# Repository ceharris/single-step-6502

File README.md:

single-step-6502
================

This repository contains KiCad sources for a simple single-step controller
module for the 6502 microprocessor. It's designed to be connected to the
system under test using jumpers. It has a pin header that provides +5 VDC,
ground, and the 6502's SYNC and RDY signal paths.

The controller has two push buttons.

1. **Run/Stop** -- is used to toggle between the free running and 
   single-step modes. In the free running mode, the green status LED is 
   illuminated.
2. **Step** -- is used to advance the processor by a single instruction when
   the CPU is stopped. While the CPU is stopped, the red status LED is 
   illuminated.

The buttons are debounced via the 555 and 74123 ICs to avoid triggering
multiple step pulses.

The circuit is designed with a diode such that it can be connected to the 
6502's RDY input without disrupting other uses of the signal.

See [single-step-6502.pdf](single-step-6502.pdf) for a full description
of the circuit design.

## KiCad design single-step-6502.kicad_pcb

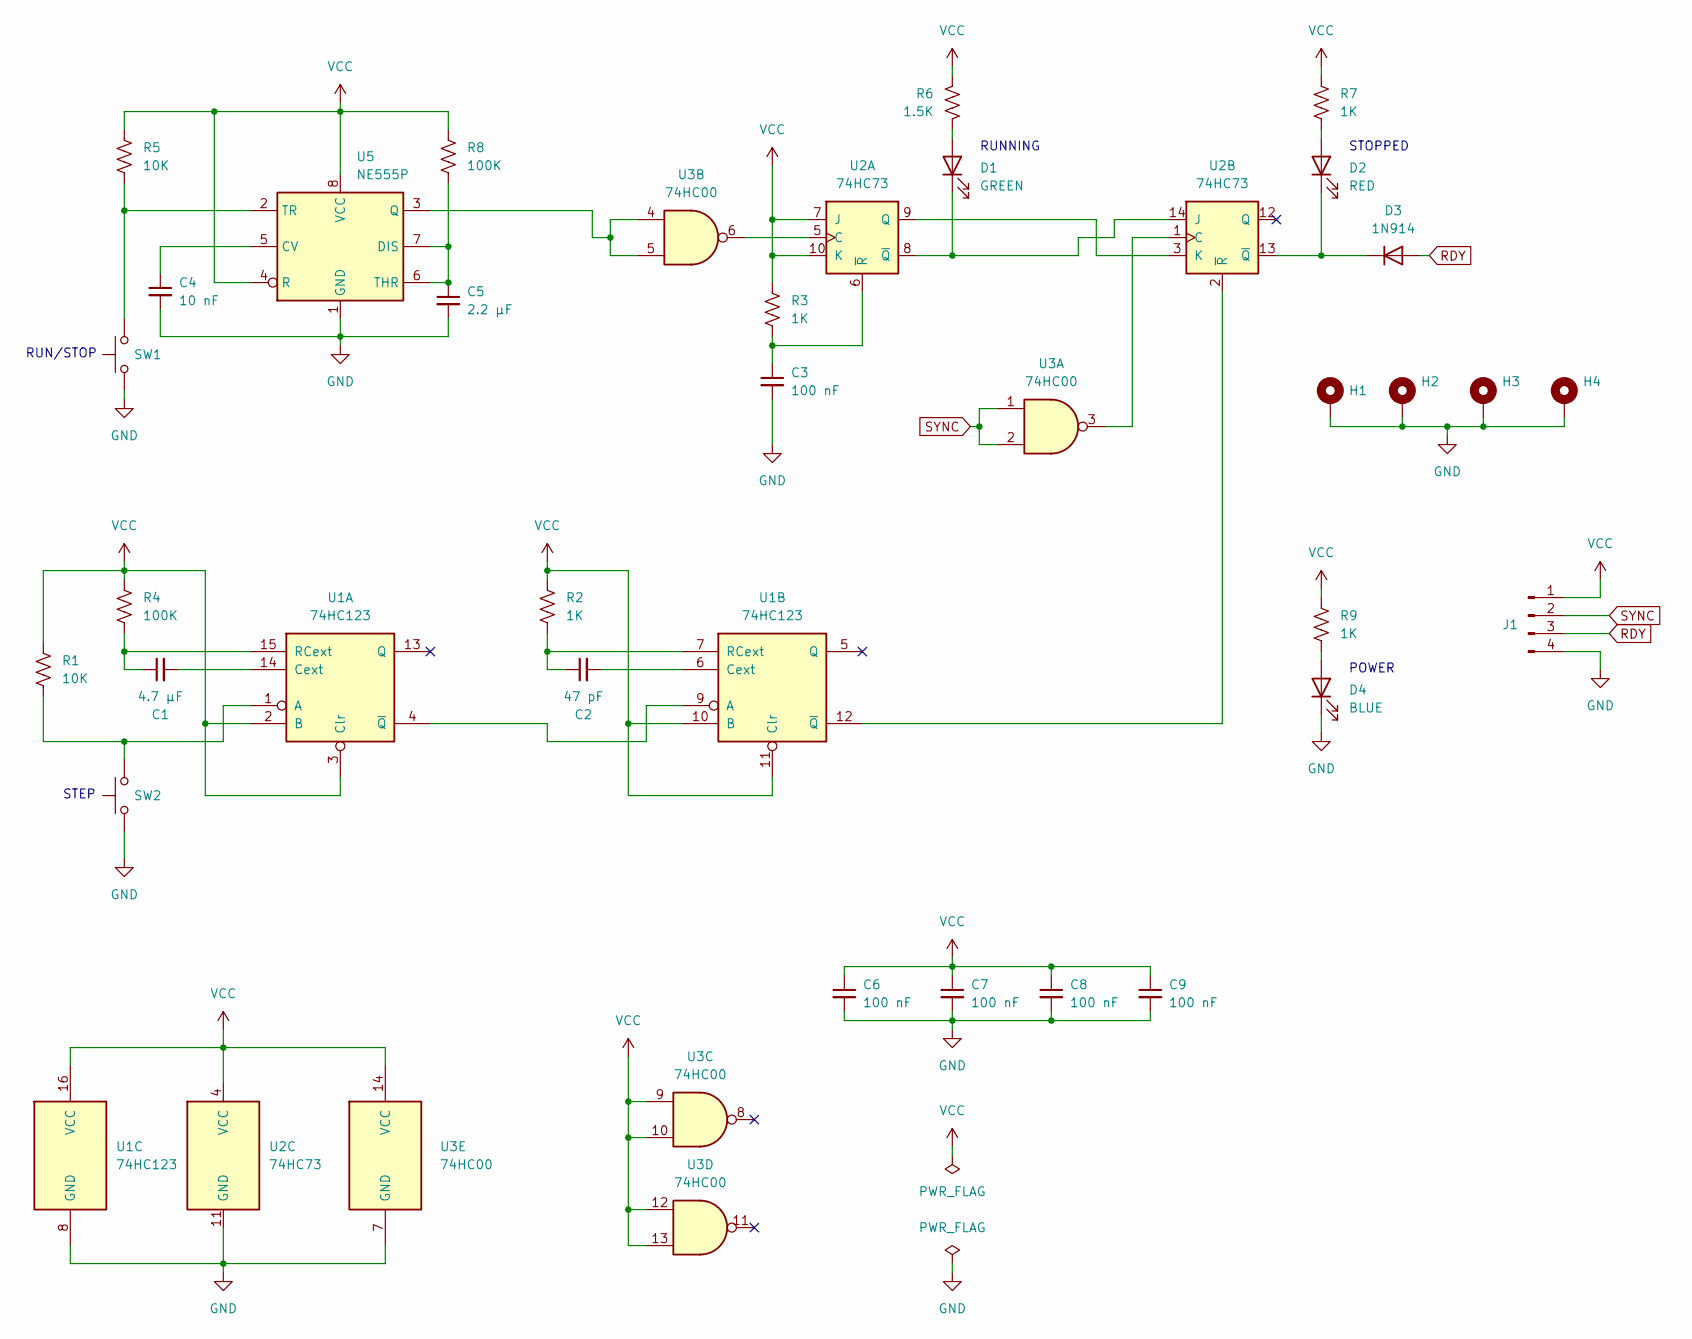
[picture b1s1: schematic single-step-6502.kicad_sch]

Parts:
C1: 4.7 µF; C_Disc_D5.0mm_W2.5mm_P2.50mm
C2: 47 pF; C_Disc_D5.0mm_W2.5mm_P2.50mm
C3, C6, C7, C8, C9: 100 nF; C_Disc_D5.0mm_W2.5mm_P2.50mm
C4: 10 nF; C_Disc_D5.0mm_W2.5mm_P2.50mm
C5: 2.2 µF; C_Disc_D5.0mm_W2.5mm_P2.50mm
D1: GREEN; LED_D5.0mm
D2: RED; LED_D5.0mm
D3: 1N914; D_A-405_P7.62mm_Horizontal
D4: BLUE; LED_D5.0mm
H1, H2, H3, H4: MountingHole_Pad; MountingHole_2.2mm_M2_DIN965_Pad
J1: Conn_01x04_Pin; PinHeader_1x04_P2.54mm_Horizontal
R1, R5: 10K; R_Axial_DIN0207_L6.3mm_D2.5mm_P7.62mm_Horizontal
R2, R3, R7, R9: 1K; R_Axial_DIN0207_L6.3mm_D2.5mm_P7.62mm_Horizontal
R4, R8: 100K; R_Axial_DIN0207_L6.3mm_D2.5mm_P7.62mm_Horizontal
R6: 1.5K; R_Axial_DIN0207_L6.3mm_D2.5mm_P7.62mm_Horizontal
SW1: SW_Push; SW_PUSH_6mm
SW2: SW_Push; SW_PUSH-12mm
U1: 74HC123; DIP-16_W7.62mm_Socket
U2: 74HC73; DIP-14_W7.62mm_Socket
U3: 74HC00; DIP-14_W7.62mm_Socket
U5: NE555P; DIP-8_W7.62mm_Socket

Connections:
GND: C3.2, C4.2, C5.2, C6.2, C7.2, C8.2, C9.2, D4.1 (K), H1.1, H2.1, H3.1, H4.1, J1.4, SW1.1, SW2.1, U1.8 (GND), U2.11 (GND), U3.7 (GND), U5.1 (GND)
unnamed: D1.2 (A), R6.2
unnamed: D1.1 (K), U2.8 (~Q), U2.14 (J)
unnamed: D2.2 (A), R7.2
unnamed: D2.1 (K), D3.1 (K), U2.13 (~Q)
unnamed: D4.2 (A), R9.2
unnamed: R1.2, SW2.2, U1.1 (A)
unnamed: C1.2, U1.14 (Cext)
unnamed: C1.1, R4.2, U1.15 (RCext)
unnamed: U1.4 (~Q), U1.9 (A)
unnamed: C2.2, U1.6 (Cext)
unnamed: C2.1, R2.2, U1.7 (RCext)
unnamed: U1.12 (~Q), U2.2 (~R)
unnamed: U2.5 (C), U3.6
unnamed: U2.3 (K), U2.9 (Q)
unnamed: C3.1, R3.2, U2.6 (~R)
unnamed: U2.1 (C), U3.3
unnamed: C4.1, U5.5 (CV)
unnamed: C5.1, R8.2, U5.6 (THR), U5.7 (DIS)
unnamed: U3.4, U3.5, U5.3 (Q)
unnamed: R5.2, SW1.2, U5.2 (TR)
RDY: D3.2 (A), J1.3
SYNC: J1.2, U3.1, U3.2
VCC: C6.1, C7.1, C8.1, C9.1, J1.1, R1.1, R2.1, R3.1, R4.1, R5.1, R6.1, R7.1, R8.1, R9.1, U1.2 (B), U1.3 (Clr), U1.10 (B), U1.11 (Clr), U1.16 (VCC), U2.4 (VCC), U2.7 (J), U2.10 (K), U3.9, U3.10, U3.12, U3.13, U3.14 (VCC), U5.4 (R), U5.8 (VCC)

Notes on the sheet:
STOPPED
POWER
RUN/STOP
RUNNING
STEP

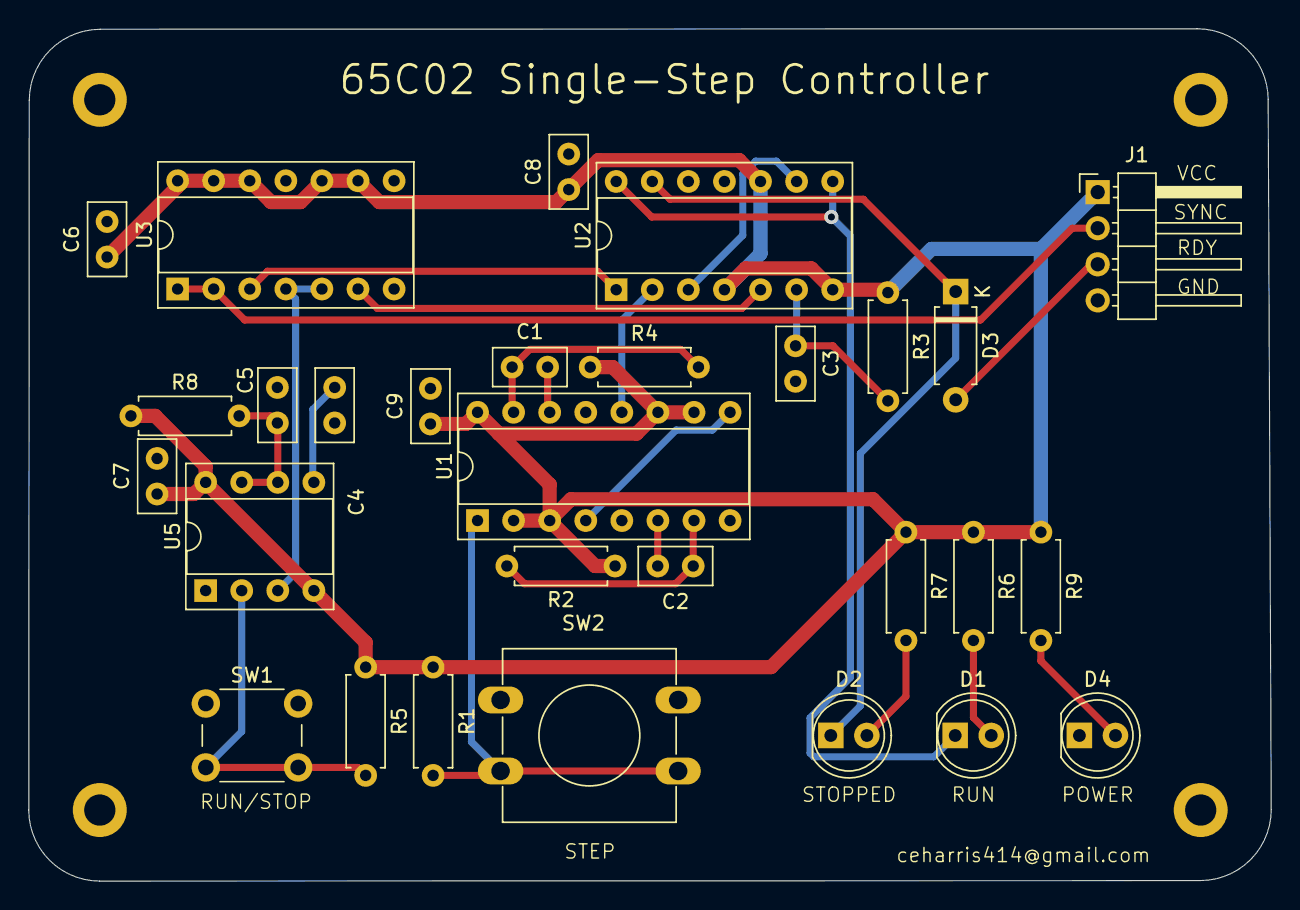
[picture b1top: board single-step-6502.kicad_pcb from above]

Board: 2 copper layers, 87.5 x 60.0 mm, 33 parts (0 on the bottom side), 24 nets.

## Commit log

2025-05-27 rename README to README.md
2025-05-27 replace board image
2025-05-27 added a few details to the README
2025-06-24 add design document
2025-06-24 add link to design document
